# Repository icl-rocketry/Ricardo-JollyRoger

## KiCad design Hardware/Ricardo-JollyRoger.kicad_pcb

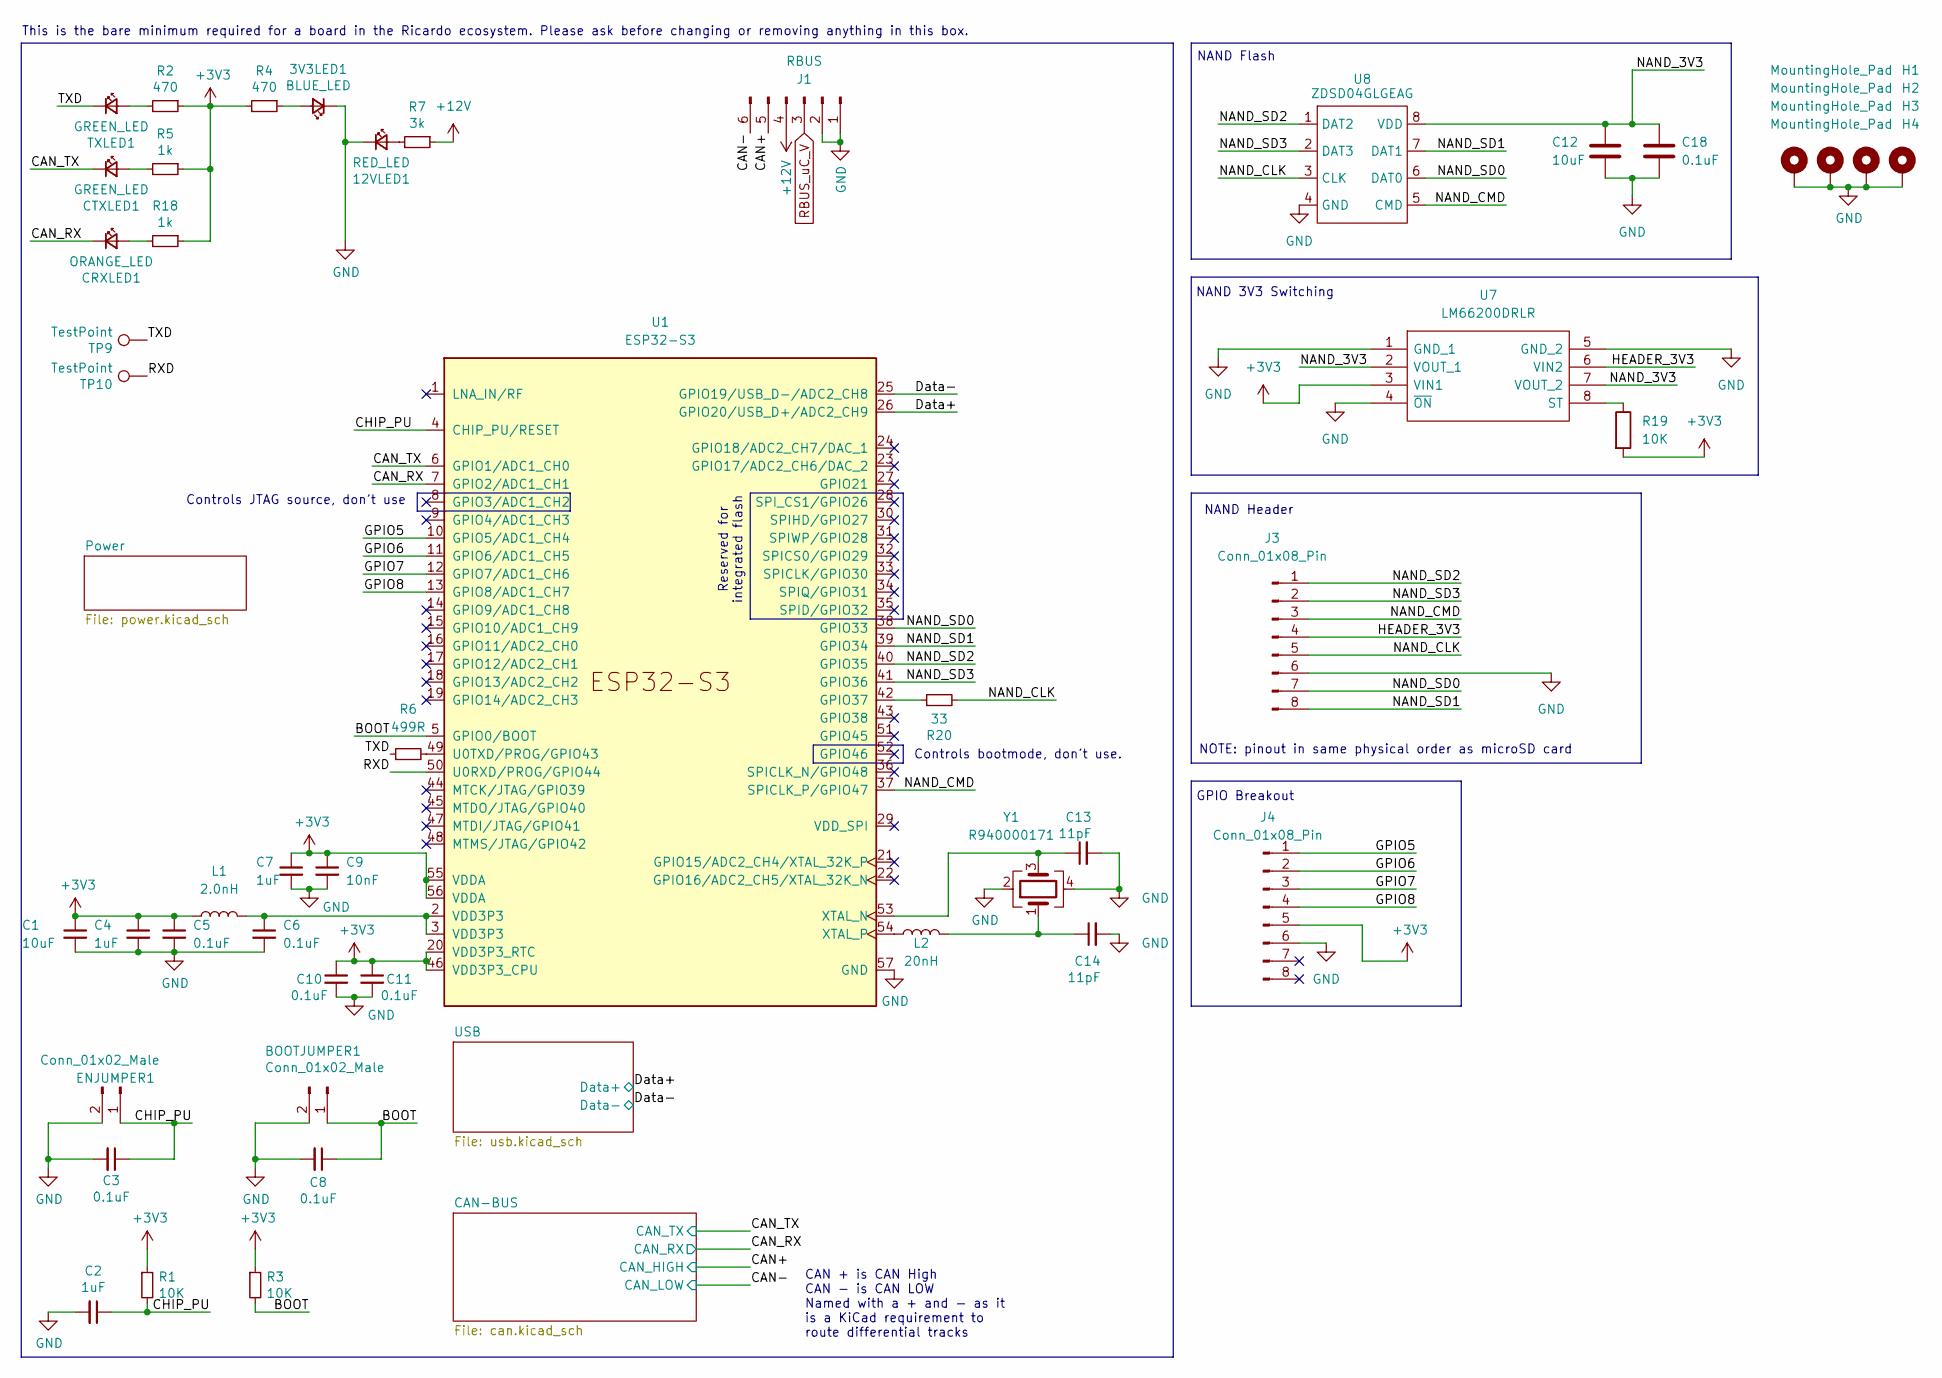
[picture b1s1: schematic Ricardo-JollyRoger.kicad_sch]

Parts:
3V3LED1: BLUE_LED; LED_0402_1005Metric
12VLED1: RED_LED; LED_0402_1005Metric
BOOTJUMPER1: Conn_01x02_Male; PinHeader_1x02_P2.54mm_Vertical
C1, C12: 10uF; C_0402_1005Metric
C2, C4, C7: 1uF; C_0402_1005Metric
C3, C5, C6, C8, C10, C11, C18: 0.1uF; C_0402_1005Metric
C9: 10nF; C_0402_1005Metric
C13, C14: 11pF; C_0402_1005Metric
CRXLED1: ORANGE_LED; LED_0402_1005Metric
CTXLED1: GREEN_LED; LED_0402_1005Metric
ENJUMPER1: Conn_01x02_Male; PinHeader_1x02_P2.54mm_Vertical
H1, H2, H3, H4: MountingHole_Pad; MountingHole_3.2mm_M3_DIN965_Pad
J1: RBUS; Molex_Mini-Fit_Jr_5566-06A_2x03_P4.20mm_Vertical
J3, J4: Conn_01x08_Pin; Molex_Pico-Clasp_202396-0807_1x08-1MP_P1.00mm_Horizontal
L1: 2.0nH; L_0402_1005Metric
L2: 20nH; L_0402_1005Metric
R1, R3, R19: 10K; R_0402_1005Metric
R2, R4: 470; R_0402_1005Metric
R5, R18: 1k; R_0402_1005Metric
R6: 499R; R_0402_1005Metric
R7: 3k; R_0402_1005Metric
R20: 33; R_0402_1005Metric
TP9, TP10: TestPoint; TestPoint_Pad_D1.0mm
TXLED1: GREEN_LED; LED_0402_1005Metric
U1: ESP32-S3; QFN40P700X700X90-57N
U7: LM66200DRLR; SOTFL50P160X60-8N; Manufacturer_Part_Number LM66200DRLR; Mouser Part Number 595-LM66200DRLR
U8: ZDSD04GLGEAG; LGA-8_8x6mm_P1.27mm
Y1: R940000171; Crystal_SMD_2016-4Pin_2.0x1.6mm

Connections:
+3V3: C1.1, C4.1, C5.1, C7.1, C9.1, C10.1, C11.1, J4.5, L1.1, R1.1, R2.1, R3.1, R4.2, R5.1, R18.1, R19.2, U1.20 (VDD3P3_RTC), U1.46 (VDD3P3_CPU), U1.55 (VDDA), U1.56 (VDDA), U7.3 (VIN1); also elsewhere on the board
+12V: J1.4, R7.1
/BOOT: BOOTJUMPER1.1, C8.1, R3.2, U1.5 (GPIO0/BOOT)
/CAN+: J1.5; also elsewhere on the board
/CAN-: J1.6; also elsewhere on the board
/CAN_RX: CRXLED1.1 (K), U1.7 (GPIO2/ADC1_CH1); also elsewhere on the board
/CAN_TX: CTXLED1.1 (K), U1.6 (GPIO1/ADC1_CH0); also elsewhere on the board
/CHIP_PU: C2.1, C3.1, ENJUMPER1.1, R1.2, U1.4 (CHIP_PU/RESET)
/Data+: U1.26 (GPIO20/USB_D+/ADC2_CH9); also elsewhere on the board
/Data-: U1.25 (GPIO19/USB_D-/ADC2_CH8); also elsewhere on the board
/GPIO5: J4.1, U1.10 (GPIO5/ADC1_CH4)
/GPIO6: J4.2, U1.11 (GPIO6/ADC1_CH5)
/GPIO7: J4.3, U1.12 (GPIO7/ADC1_CH6)
/GPIO8: J4.4, U1.13 (GPIO8/ADC1_CH7)
/HEADER_3V3: J3.4, U7.6 (VIN2)
/NAND_3V3: C12.1, C18.1, U7.2 (VOUT_1), U7.7 (VOUT_2), U8.8 (VDD)
/NAND_CLK: J3.5, R20.2, U8.3 (CLK)
/NAND_CMD: J3.3, U1.37 (SPICLK_P/GPIO47), U8.5 (CMD)
/NAND_SD0: J3.7, U1.38 (GPIO33), U8.6 (DAT0)
/NAND_SD1: J3.8, U1.39 (GPIO34), U8.7 (DAT1)
/NAND_SD2: J3.1, U1.40 (GPIO35), U8.1 (DAT2)
/NAND_SD3: J3.2, U1.41 (GPIO36), U8.2 (DAT3)
/RXD: TP10.1, U1.50 (U0RXD/PROG/GPIO44)
/TXD: R6.1, TP9.1, TXLED1.1 (K)
GND: 3V3LED1.1 (K), 12VLED1.1 (K), BOOTJUMPER1.2, C1.2, C2.2, C3.2, C4.2, C5.2, C6.2, C7.2, C8.2, C9.2, C10.2, C11.2, C12.2, C13.2, C14.2, C18.2, ENJUMPER1.2, H1.1, H2.1, H3.1, H4.1, J1.1, J1.2, J3.6, J4.6, U1.57 (GND), U7.1 (GND_1), U7.4 (~ON), U7.5 (GND_2), U8.4 (GND), Y1.2, Y1.4; also elsewhere on the board
unnamed: 3V3LED1.2 (A), R4.1
unnamed: 12VLED1.2 (A), R7.2
unnamed: C6.1, L1.2, U1.2 (VDD3P3), U1.3 (VDD3P3)
unnamed: C14.1, L2.2, Y1.1
unnamed: CRXLED1.2 (A), R18.2
unnamed: CTXLED1.2 (A), R5.2
unnamed: R2.2, TXLED1.2 (A)
unnamed: R20.1, U1.42 (GPIO37)
unnamed: R6.2, U1.49 (U0TXD/PROG/GPIO43)
unnamed: C13.1, U1.53 (XTAL_N), Y1.3
unnamed: L2.1, U1.54 (XTAL_P)
unnamed: R19.1, U7.8 (ST)
RBUS_uC_V: J1.3; also elsewhere on the board

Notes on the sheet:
Controls bootmode, don't use.
NAND Flash
This is the bare minimum required for a board in the Ricardo ecosystem. Please ask before changing or removing anything in this box.
CAN + is CAN High CAN - is CAN LOW Named with a + and - as it is a KiCad requirement to route differential tracks
NOTE: pinout in same physical order as microSD card
NAND 3V3 Switching
GPIO Breakout
Controls JTAG source, don't use
Reserved for integrated flash
NAND Header

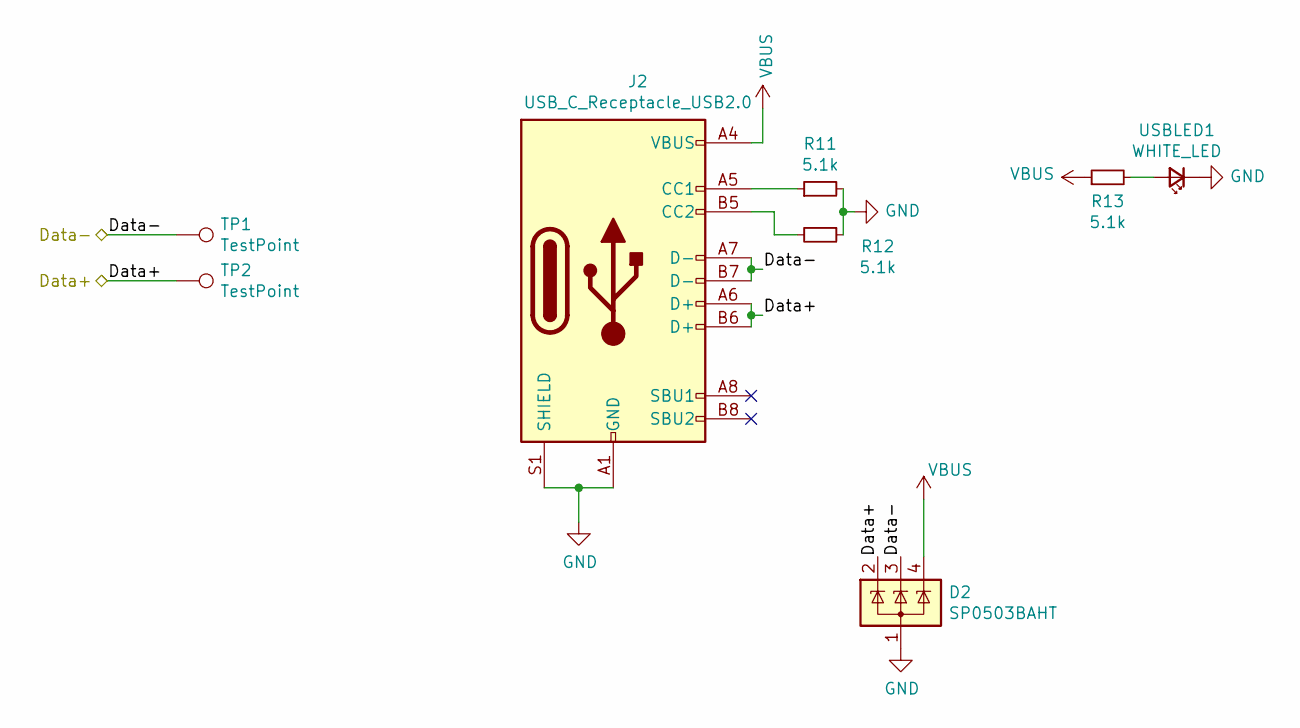
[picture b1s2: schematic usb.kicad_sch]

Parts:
D2: SP0503BAHT; SOT-143
J2: USB_C_Receptacle_USB2.0; USB_C_Receptacle_Palconn_UTC16-G
R11, R12, R13: 5.1k; R_0402_1005Metric
TP1, TP2: TestPoint; TestPoint_Pad_D1.0mm
USBLED1: WHITE_LED; LED_0402_1005Metric

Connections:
/Data+: D2.2 (K), J2.A6 (D+), J2.B6 (D+), TP2.1; also elsewhere on the board
/Data-: D2.3 (K), J2.A7 (D-), J2.B7 (D-), TP1.1; also elsewhere on the board
GND: D2.1 (A), J2.A1 (GND), J2.A12 (GND), J2.B1 (GND), J2.B12 (GND), J2.S1 (SHIELD), R11.2, R12.1, USBLED1.1 (K); also elsewhere on the board
unnamed: J2.A5 (CC1), R11.1
unnamed: J2.B5 (CC2), R12.2
unnamed: R13.2, USBLED1.2 (A)
VBUS: D2.4 (K), J2.A4 (VBUS), J2.A9 (VBUS), J2.B4 (VBUS), J2.B9 (VBUS), R13.1; also elsewhere on the board

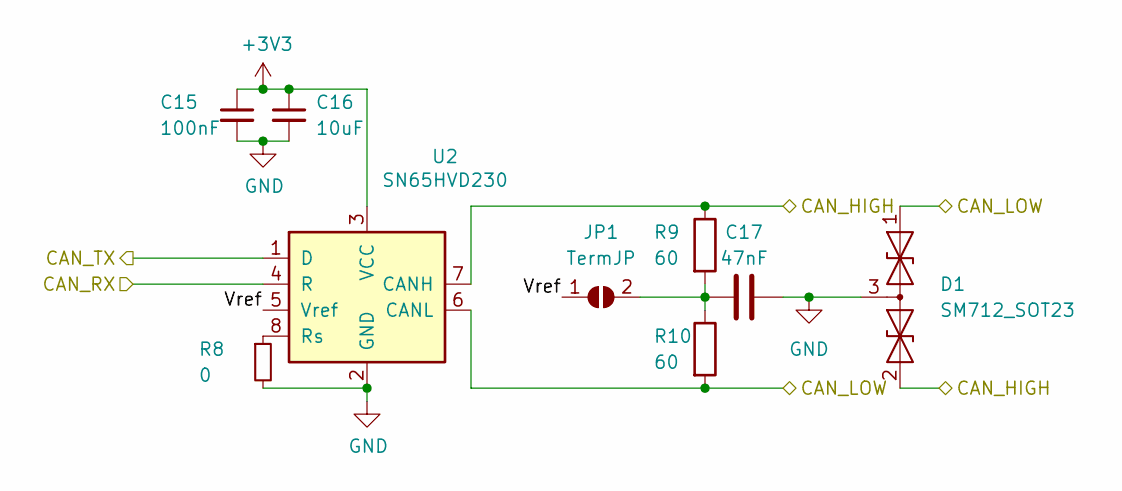
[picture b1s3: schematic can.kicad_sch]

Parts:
C15: 100nF; C_0402_1005Metric
C16: 10uF; C_0402_1005Metric
C17: 47nF; C_0402_1005Metric
D1: SM712_SOT23; SOT-23
JP1: TermJP; SolderJumper-2_P1.3mm_Open_RoundedPad1.0x1.5mm
R8: 0; R_0402_1005Metric
R9, R10: 60; R_0603_1608Metric
U2: SN65HVD230; SOIC-8_3.9x4.9mm_P1.27mm

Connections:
+3V3: C15.1, C16.1, U2.3 (VCC); also elsewhere on the board
/CAN+: D1.2 (A2), R9.1, U2.7 (CANH); also elsewhere on the board
/CAN-: D1.1 (A1), R10.2, U2.6 (CANL); also elsewhere on the board
/CAN-BUS/Vref: JP1.1 (A), U2.5 (Vref)
/CAN_RX: U2.4 (R); also elsewhere on the board
/CAN_TX: U2.1 (D); also elsewhere on the board
GND: C15.2, C16.2, C17.2, D1.3 (common), R8.2, U2.2 (GND); also elsewhere on the board
unnamed: C17.1, JP1.2 (B), R9.2, R10.1
unnamed: R8.1, U2.8 (Rs)

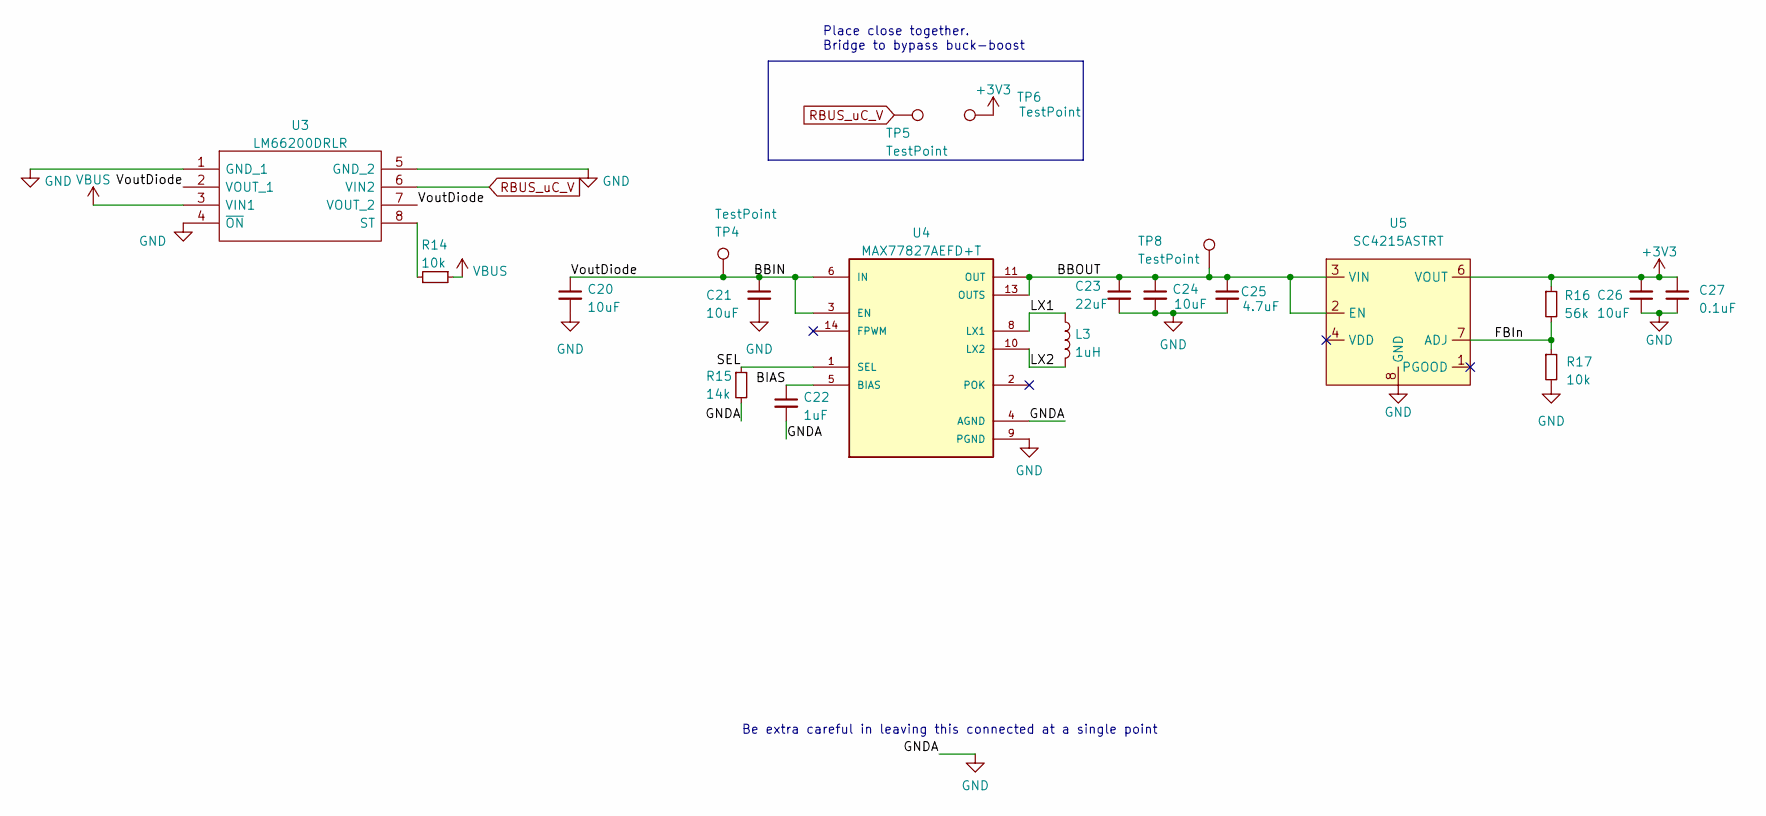
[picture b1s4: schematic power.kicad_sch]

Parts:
C20, C24, C26: 10uF; C_0402_1005Metric
C21: 10uF; C_0603_1608Metric
C22: 1uF; C_0402_1005Metric
C23: 22uF; C_0603_1608Metric
C25: 4.7uF; C_0402_1005Metric
C27: 0.1uF; C_0402_1005Metric
L3: 1uH; L_0805_2012Metric
R14, R17: 10k; R_0402_1005Metric
R15: 14k; R_0402_1005Metric
R16: 56k; R_0402_1005Metric
TP4, TP5, TP6, TP8: TestPoint; TestPoint_Pad_D1.5mm
U3: LM66200DRLR; SOTFL50P160X60-8N; Manufacturer_Part_Number LM66200DRLR; Mouser Part Number 595-LM66200DRLR
U4: MAX77827AEFD+T; CONV_MAX77827AEFD+T; PARTREV B
U5: SC4215ASTRT; SOIC127P599X175-9N

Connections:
+3V3: C26.2, C27.2, R16.1, TP6.1, U5.6 (VOUT); also elsewhere on the board
/Power/BBIN: C20.1, C21.1, TP4.1, U3.2 (VOUT_1), U3.7 (VOUT_2), U4.3 (EN), U4.6 (IN)
/Power/BBOUT: C23.1, C24.1, C25.1, TP8.1, U4.11 (OUT), U4.13 (OUTS), U5.2 (EN), U5.3 (VIN)
/Power/BIAS: C22.1, U4.5 (BIAS)
/Power/FBIn: R16.2, R17.1, U5.7 (ADJ)
/Power/LX1: L3.1, U4.8 (LX1)
/Power/LX2: L3.2, U4.10 (LX2)
/Power/SEL: R15.1, U4.1 (SEL)
GND: C20.2, C21.2, C22.2, C23.2, C24.2, C25.2, C26.1, C27.1, R15.2, R17.2, U3.1 (GND_1), U3.4 (~ON), U3.5 (GND_2), U4.4 (AGND), U4.9 (PGND), U5.8 (GND), U5.9 (GND); also elsewhere on the board
unnamed: R14.2, U3.8 (ST)
RBUS_uC_V: TP5.1, U3.6 (VIN2); also elsewhere on the board
VBUS: R14.1, U3.3 (VIN1); also elsewhere on the board

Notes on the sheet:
Place close together. Bridge to bypass buck-boost
Be extra careful in leaving this connected at a single point

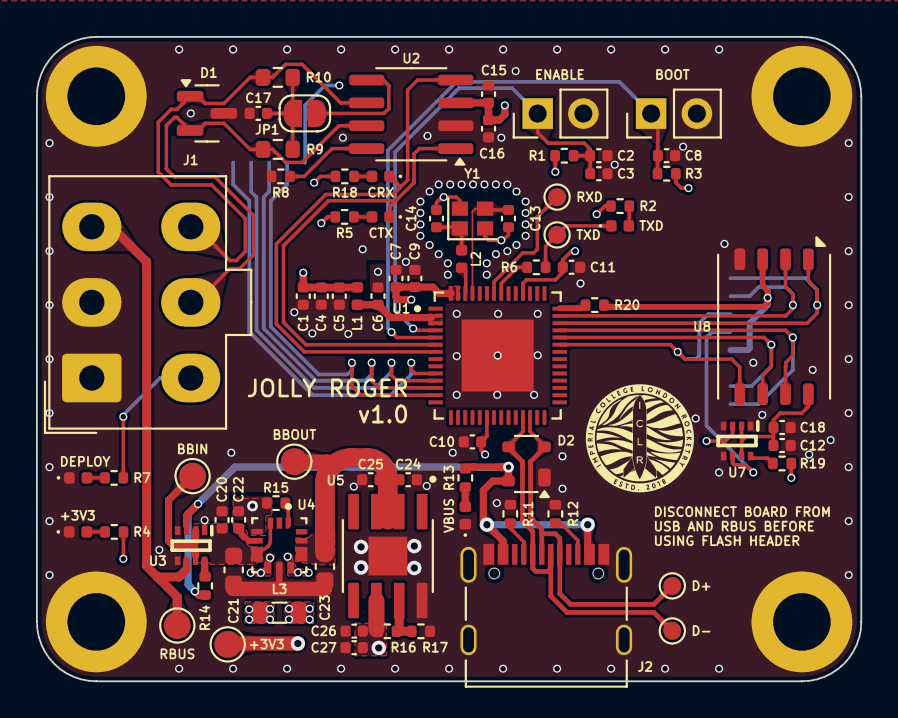
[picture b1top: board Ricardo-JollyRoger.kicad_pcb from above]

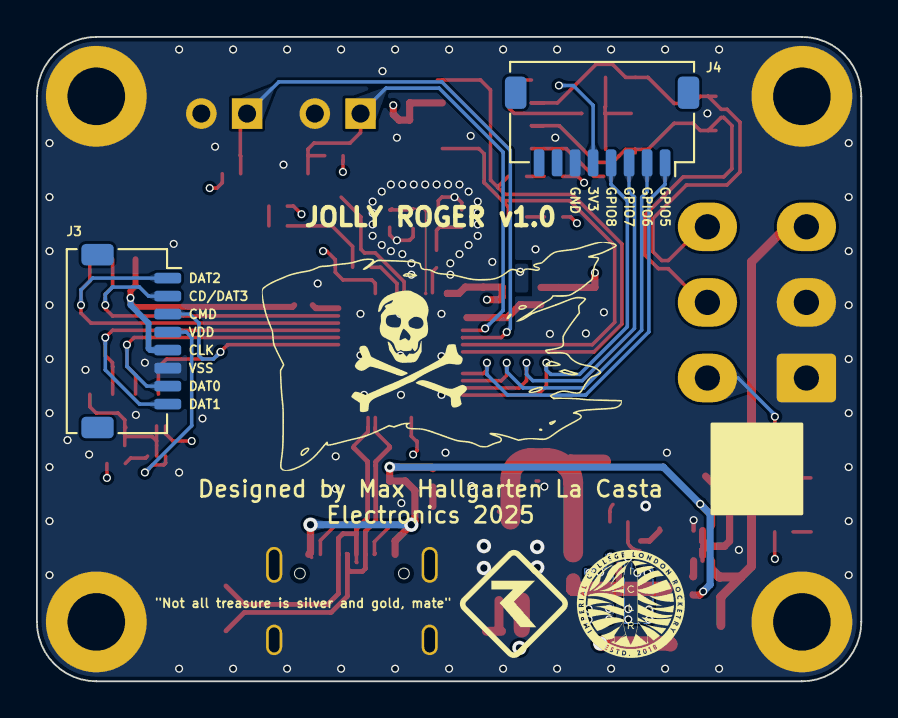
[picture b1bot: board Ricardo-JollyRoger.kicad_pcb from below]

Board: 4 copper layers, 45.8 x 35.8 mm, 84 parts (3 on the bottom side), 53 nets.

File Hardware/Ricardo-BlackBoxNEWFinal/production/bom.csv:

Designator,Footprint,Quantity,Value,LCSC Part #
3V3LED1,0402,1,BLUE_LED,
"BOOTJUMPER1, ENJUMPER1",PinHeader_1x02_P2.54mm_Vertical,2,Conn_01x02_Male,
"C1, C16, C20, C24, C26, C28",0402,6,10uF,
"C10, C11, C27, C29, C3, C5, C6, C8",0402,8,0.1uF,
"C12, R5",0402,2,DNP,
"C13, C14",0402,2,11pF,
C15,0402,1,100nF,
C17,0402,1,47nF,
"C2, C22, C4, C7",0402,4,1uF,
C21,0603,1,10uF,
C23,0603,1,22uF,
C25,0402,1,4.7uF,
C9,0402,1,10nF,
D1,SOT-23,1,SM712_SOT23,
D2,SOT-143,1,SP0503BAHT,
"H1, H2, H3, H4",MountingHole_3.2mm_M3_DIN965_Pad,4,MountingHole_Pad,
IC1,SON127P800X600X95-8N,1,XTSD08GLGEAG,
J1,Molex_Mini-Fit_Jr_5566-06A_2x03_P4.20mm_Vertical,1,RBUS,
J2,USB_C_Receptacle_Palconn_UTC16-G,1,USB_C_Receptacle_USB2.0,
JP1,SolderJumper-2_P1.3mm_Open_RoundedPad1.0x1.5mm,1,TermJP,
L1,0402,1,2.0nH,
L2,0402,1,20nH,
L3,0805,1,1uH,
"R1, R14, R17, R3",0402,4,10K,
"R10, R9",0603,2,60,
"R11, R12",0402,2,5.1k,
"R13, R2, R4",0402,3,470,
R15,0402,1,14k,
R16,0402,1,56k,
R6,0402,1,499,
R8,0603,1,0,
"TP1, TP10, TP11, TP12, TP13, TP2, TP3, TP9",TestPoint_Pad_D1.0mm,8,TestPoint,
"TP4, TP5, TP6, TP7, TP8",TestPoint_Pad_D1.5mm,5,TestPoint,
TXLED1,0402,1,GREEN_LED,
U1,QFN40P700X700X90-57N,1,ESP32-S3,
U2,SOIC-8_3.9x4.9mm_P1.27mm,1,SN65HVD230,
U3,SOTFL50P160X60-8N,1,LM66200DRLR,
U4,CONV_MAX77827AEFD+T,1,MAX77827AEFD+T,
U5,SOIC127P599X175-9N,1,SC4215,
USBLED1,0402,1,USB_LED,
Y1,Crystal_SMD_2016-4Pin_2.0x1.6mm,1,40MHz±10ppm,

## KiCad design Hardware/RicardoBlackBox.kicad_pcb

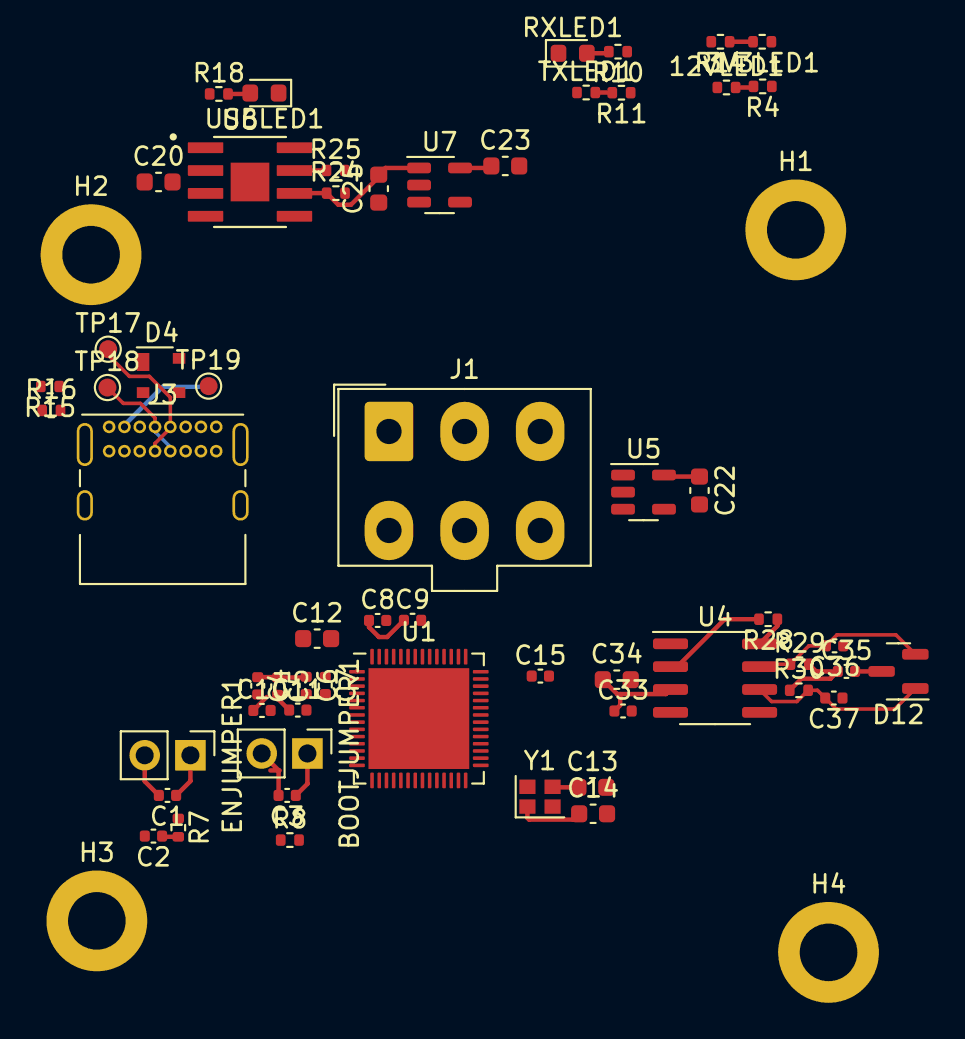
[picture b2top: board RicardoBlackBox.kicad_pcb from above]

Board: 2 copper layers, 62 parts (0 on the bottom side), 26 nets.

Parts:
3V3LED1: 3V3LED; R_0402_1005Metric
12VLED1: 12V_LED; R_0402_1005Metric
BOOTJUMPER1: Conn_01x02_Male; PinHeader_1x02_P2.54mm_Vertical
C1, C3, C6, C7, C10, C11, C35: 0.1uF; C_0402_1005Metric
C2, C5, C8: 1uF; C_0402_1005Metric
C4, C15: 10uF; C_0402_1005Metric
C9: 10nF; C_0402_1005Metric
C12, C13, C14: C; C_0603_1608Metric
C20, C25, C34: 10uF; C_0603_1608Metric
C22, C23: 4.7uF; C_0603_1608Metric
C33: 100nF; C_0402_1005Metric
C36: 220pF; C_0402_1005Metric
C37: 220 pF; C_0402_1005Metric
D4: SP0503BAHT; SOT-143
D12: SM712_SOT23; SOT-23
ENJUMPER1: Conn_01x02_Male; PinHeader_1x02_P2.54mm_Vertical
H1, H2, H3, H4: MountingHole_Pad; MountingHole_3.2mm_M3_DIN965_Pad
J1: RBUS; Molex_Mini-Fit_Jr_5566-06A_2x03_P4.20mm_Vertical
J3: USB_C_Receptacle_USB2.0; USB_C_Receptacle_GCT_USB4085
R4: 3k; R_0402_1005Metric
R7, R8: 10K; R_0402_1005Metric
R10, R11, R14, R18: 470; R_0402_1005Metric
R15, R16: 5.1k; R_0402_1005Metric
R24: 56k; R_0402_1005Metric
R25, R28: 10k; R_0402_1005Metric
R29, R30: 60; R_0402_1005Metric
RXLED1: RX_LED; LED_0603_1608Metric
TP17, TP18, TP19: TestPoint; TestPoint_Pad_D1.0mm
TXLED1: TX_LED; R_0402_1005Metric
U1: ESP32-S3; QFN-56-1EP_7x7mm_P0.4mm_EP5.6x5.6mm
U4: SN65HVD230; SOIC-8_3.9x4.9mm_P1.27mm
U5, U7: LTC4411; SOT-23-5
U6: SC4216H; SOIC127P599X175-9N
USBLED1: USB_LED; LED_0603_1608Metric
Y1: 40MHz±10ppm; Crystal_SMD_2016-4Pin_2.0x1.6mm

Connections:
+3V3: C4.1, C5.1, C6.1, C8.1, C9.1, C10.1, C11.1, C15.1, C22.1, C23.1, C33.1, C34.1, R7.1, R8.1, R10.1, R11.1, R14.2, U1.20 (VDD3P3_RTC), U1.46 (VDD3P3_CPU), U1.55 (VDDA), U1.56 (VDDA), U4.3 (VCC), U5.5 (OUT), U7.5 (OUT)
+12V: J1.4, R4.1
/BOOT: BOOTJUMPER1.1, C3.1, R8.2, U1.5 (GPIO0/BOOT)
/CAN+: C36.2, D12.2 (A2), J1.5, R29.1, U4.7 (CANH)
/CAN-: C37.2, D12.1 (A1), J1.6, R30.2, U4.6 (CANL)
/CHIP_PU: C1.1, C2.1, ENJUMPER1.1, R7.2, U1.4 (CHIP_PU/RESET)
/Data+: D4.4 (K), J3.A6 (D+), J3.B6 (D+), TP18.1, U1.26 (GPIO20/USB_D+/ADC2_CH9)
/Data-: D4.3 (K), J3.A7 (D-), J3.B7 (D-), TP17.1, U1.25 (GPIO19/USB_D-/ADC2_CH8)
GND: 3V3LED1.1 (K), 12VLED1.1 (K), BOOTJUMPER1.2, C1.2, C2.2, C3.2, C4.2, C5.2, C6.2, C7.2, C8.2, C9.2, C10.2, C11.2, C13.2, C14.2, C20.1, C22.2, C23.2, C25.1, C33.2, C34.2, C35.2, C36.1, C37.1, D4.1 (A), D12.3 (common), ENJUMPER1.2, H1.1, H2.1, H3.1, H4.1, J1.1, J1.2, J3.A1 (GND), J3.A12 (GND), J3.B1 (GND), J3.B12 (GND), J3.S1 (SHIELD), R15.2, R16.1, R25.2, R28.2, U1.57 (GND), U4.2 (GND), U5.2 (GND), U5.3 (CTL), U6.8 (GND), U6.9 (GND), U7.2 (GND), U7.3 (CTL), USBLED1.1 (K), Y1.2, Y1.4
unnamed: 3V3LED1.2 (A), R14.1
unnamed: 12VLED1.2 (A), R4.2
unnamed: C7.1, U1.2 (VDD3P3), U1.3 (VDD3P3)
unnamed: C12.2, U1.1 (LNA_IN/RF)
unnamed: C13.1, U1.53 (XTAL_N), Y1.3
unnamed: C14.1, Y1.1
unnamed: C25.2, R24.1, U6.6 (VOUT), U7.1 (IN)
unnamed: C35.1, R29.2, R30.1
unnamed: J1.3, U5.1 (IN)
unnamed: J3.A5 (CC1), R15.1
unnamed: J3.B5 (CC2), R16.2
unnamed: R10.2, RXLED1.2 (A)
unnamed: R11.2, TXLED1.2 (A)
unnamed: R18.2, USBLED1.2 (A)
unnamed: R24.2, R25.1, U6.7 (ADJ)
unnamed: R28.1, U4.8 (Rs)
VBUS: C20.2, D4.2 (K), J3.A4 (VBUS), J3.A9 (VBUS), J3.B4 (VBUS), J3.B9 (VBUS), R18.1, TP19.1, U6.2 (EN), U6.3 (VIN)

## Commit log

2025-01-07 Ricardo-BlackBox
    Ricardo-BlackBox
    PushingSecondSchematic
    push3schematicandpcb
    4th
    NewESP32RicardoBlackBox
    AsOf13/12/2022
2025-01-07 Moved decoupling capacitors
2025-01-07 Moved USB test pads
2025-01-07 Rearranging ESP32 CLC
2025-01-07 Removed README
2025-01-07 Add method for time since boot
2025-01-07 Ensure VBUS connections after ESD protection
2025-01-07 Update documentation
2025-01-07 Moved CAN RX/TX lines
2025-01-07 Update crystal exclusion zone and grounding
2025-01-07 Add simple time update
2025-01-07 Ignore backup zips
2025-01-07 Single end byte
2025-01-07 Updated directory structure
2025-01-07 Move TXD/RXD pads
2025-01-07 Added methods to retrieve volume statistics
2025-01-07 Added additional vias
2025-01-07 Updated USB data line trace widths
2025-01-07 Update zone fill for CAN chip
2025-01-07 Add .gitignore
2025-01-07 Increased VBUS trace widths and rerouted
2025-01-07 Refactor as time service class
2025-01-07 Hoisted the colours
2025-01-07 Initial packet logging implementation
2025-01-07 Updated RBUS trace
2025-01-07 Updated buckboost silkscreen labels
2025-01-07 Update length matching
2025-01-07 Switch to SdFat fork
2025-01-07 Increase packet log buffer size
2025-01-07 Basic heartbeat implementation
2025-01-07 Update submodule commits
2025-01-07 Add metadata to binary log
2025-01-07 Move NAND flash chip
2025-01-07 Changed NAND flash to ZDSD04GLGEAG
2025-01-07 Purge firmware
2025-01-07 Initial hardware update
2025-01-07 Kermit Mini pinmap
2025-01-07 Removed data line switching and rearranged
2025-01-07 Update silkscreen labels for LEDs and pads
2025-01-07 Reduced XO trace width
2025-01-07 Switched to PicoBlade connector
2025-01-07 Typo
2025-01-07 Fixed fill zones
2025-01-07 Rearranged NAND 3V3 switching and fixed buck-boost overlaps
2025-01-07 System time getter and setter in millis
2025-01-07 Changed to PicoClasp connector
2025-01-07 Fixed zone priorities
2025-01-07 Initial telemetry implementation
2025-01-07 Log system time
2025-01-07 Add submodules
2025-01-07 Additional submodule commit update
2025-01-07 Moved NAND flash chip and added debounce resistor
2025-01-07 Pull sdkconfig updates from Kermit v3-DEV
2025-01-07 Update name position
2025-01-07 Updated KiCad filenames
2025-01-20 Tweaked trace
2025-01-20 Added additional GND vias
2025-01-20 Made deployment LED label generic
2025-01-20 Moved C11 closer to ESP32
2025-01-20 Re-routed HEADER_3V3 trace and added via to improve the ground path between the NAND chip and the connector
2025-01-20 Added additional ground vias near the CAN chip
2025-01-20 Moved NAND power switching to reduce distance of decoupling capacitors
2025-01-20 Added quote
2025-01-25 Updated footprints
2025-01-25 Updated exclusion around XO
2025-01-25 Increase board size
2025-01-25 Added edge vias
2025-01-25 Updated NAND traces
2025-01-25 Added standalone labels for named components
2025-01-25 Updated NAND termination resistor
2025-01-25 Marked unused ESP32 pins
2025-01-26 Added labels for NAND pinout
2025-01-26 Reduce edge via size
2025-01-27 Added GPIO breakout
2025-01-28 Rearranged NAND
2025-01-28 Add warning message
2025-02-01 Upgrade GPIO breakout to four pins
2025-02-19 Update project name
2025-02-19 Pass system into idle state
2025-02-19 Added boot counter stored in NVS
2025-02-19 Replace epoch time with boot count in logged packets
2025-02-20 Initial prober implementation
2025-02-20 Update to use service identifier from configuration
2025-02-25 Initial migration
2025-02-28 Added 3V3 and GND to GPIO breakout
2025-03-01 Updated NAND flash symbol
2025-03-01 Moved 3V3 via
2025-03-04 Remove idle heartbeat
2025-03-04 Update components
2025-03-04 Added barcode square
2025-04-12 Updated capacitor layout
2025-04-12 Changed GPIO breakout to 8 pin connector
2025-04-16 Incorporated review feedback
